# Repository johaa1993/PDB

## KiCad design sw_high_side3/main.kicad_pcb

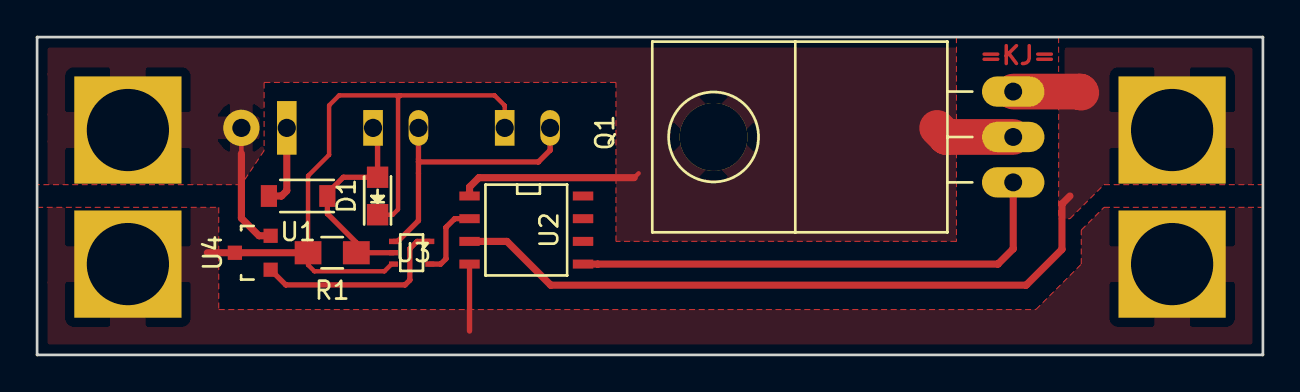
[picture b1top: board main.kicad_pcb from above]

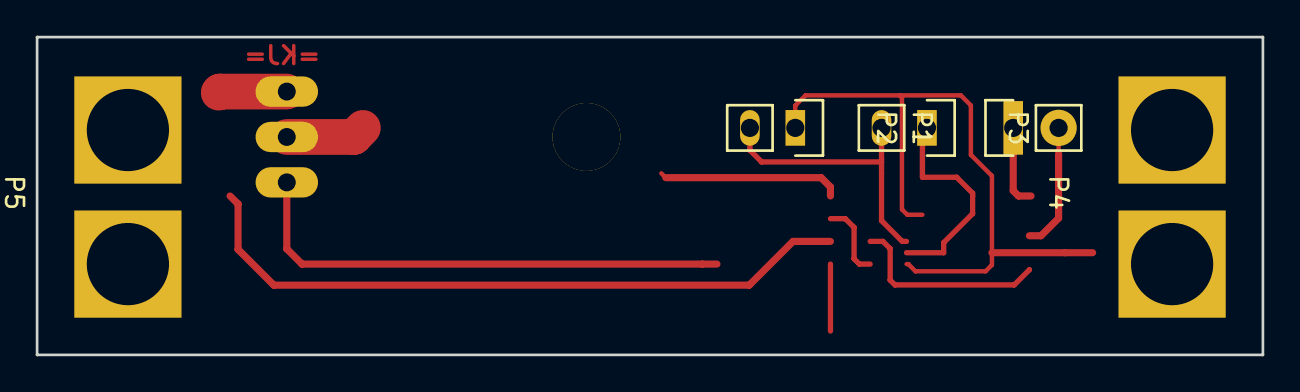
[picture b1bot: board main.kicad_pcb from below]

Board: 2 copper layers, 68.6 x 17.8 mm, 12 parts (5 on the bottom side), 9 nets.

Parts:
D1: 3.3v; LED_0805
P1, P2, P3: CONN_01X02; Pin_Header_Straight_1x02
P4, P5: CONN_XT60; XT60
Q1: IRFB7537PbF; TO-220_Horizontal_LargePads_HeatsinkPad
R1: 10k; R_0805_HandSoldering
U1: NSI45020AT1G; SOD-123
U2: MIC5014; SOIC-8-N
U3: 74LVC1G08; SOT-353
U4: LM3480-3.3; SOT-23

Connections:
/In+: P1.2, P4.2, Q1.2, U2.1, U4.2
/In-: D1.1, P2.1, P4.1, P5.1, R1.2, U2.4, U3.3, U4.3
/Out+: P5.2, Q1.3, U2.3
unnamed: D1.2, P3.1, R1.1, U1.1, U3.2
unnamed: P1.1, U1.2
unnamed: P2.2, P3.2, U3.1
unnamed: Q1.1, U2.5
unnamed: U2.2, U3.4
unnamed: U3.5, U4.1
